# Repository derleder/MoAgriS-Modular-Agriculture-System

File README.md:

# MoAgriS - Modular Agriculture System

## Introduction
MoAgriS is a System to automate plant care with the help of modules for light, water and wind. The modules are plugged onto 3 rods providing power and communication. This way they can be placed individually to fit the plants needs. The project has been developed under Windows but the use of Linux is possible and encouraged.

## Quickstart
There is none. You need to get the PCBs and the components of the [BOM](#bom) first and combine them yourself or let your provider populate everything. [LCSC](https://lcsc.com/) has been quite usefull since they offer a [PCB service](https://jlcpcb.com/) besides the components and the shipment can be combined. A possible PCB configuration can be seen in [PCB/notes/pcb-spec.PNG](./PCB/notes/pcb-spec.PNG). The default values such as PCB thickness or copper weight of 1 oz are fine, too. Unfortunately not all parts can be found there at the time of writing such as the SAMD11 or the PT4115 current regulator.

Once a PCB is ready the SAMD11 needs a [bootloader](https://github.com/mattairtech/ArduinoCore-samd/blob/master/bootloaders/zero/binaries/sam_ba_Generic_D11C14A_SAMD11C14A.bin) by [Mattairtech](https://github.com/mattairtech) to be transmitted via the SWD interface. This is a one-time procedure since the bootloader handles all the firmware updates via USB afterwards. The [Segger J-Link](https://www.segger.com/products/debug-probes/j-link/models/j-link-edu-mini/) comes in handy for that if the licensing is not a problem to you. Other solutions are possible as long as the SAMD11 is supported. Currently I use [Atmel Studio](https://www.microchip.com/mplab/avr-support/atmel-studio-7) for this step (Tools->Device Programming) though the Studio is quite an overkill.

Right now there is no Firmware binary (see [Future](#Future)) so you need to go through the [Development](#Development) section to set up the [Arduino IDE](https://www.arduino.cc/en/main/software). After that you can compile and upload the firmwares found in [Firmware](/Firmware). You need one master on the SDI bus and you can use pretty much as many slaves as you want - tell me if there's a limit. The master can be any PCB that has a SAMD11 if you wish to wish keep your order small. The dedicated master PCB only has power and BUS connectors.

Now that the PCBs are fully working it's time to clamp them on the rods. Plug the master via USB into your PC/Raspberry and open a serial console such as Realterm (Windows) or minicom (Linux). Find out the masters COM-Port (Windows: Device Manager -> COM & LPT ports -> the one thats containing Mattairtech in the description), set the Baud rate to 115200 and connect to it. You should receive a welcoming "Opening SDI-12 bus master..." the first time you connect to the master. It's best to tell your terminal to add a line feed (\n) to a command. This way the master knows to send it over the SDI bus - it's not neccessary since a command is sent anyway after a timeout of 1s.

That's it pretty much. You should be able to send commands to the individual modules now. There's a node-red solution in development to automate it further.

## Alternative Uploading
Since the USB ports are no real benefit they can be left out except for the master board which uses it for serial communication. To achieve that choose [NO_BOOTLOADER in the Arduino Tools Bootloader size menu](https://github.com/mattairtech/ArduinoCore-samd#bootloader-size-menu). After you created/exported the binaries you can use another programmer like Atmel Studio to program directly via the Segger J-Link to the very start of the flash (no address needs to be specified).

The binaries can also be found directly in the corresponding folders under Firmware.

## Development
Thanks to [Mattairtechs ArduinoCore-samd](https://github.com/mattairtech/ArduinoCore-samd) firmware development is quite easy. The setup is described [here](https://github.com/mattairtech/ArduinoCore-samd#installation) (two parts!). The flash size of the SAMD11 is quite small to fit in all the firmware but it is possible if you turn off as many functions as possible in the config.h (Windows: C:\Users\User\AppData\Local\Arduino15\packages\MattairTech_Arduino\hardware\samd\1.6.18-beta-b1\config.h). My config can be found in [Firmware/config.h](./Firmware/config.h). You will save additional flash space by setting serial config under tools to "no_uart_one_wire_one_spi".

You also need to install [Arduino-SDI-12](https://github.com/EnviroDIY/Arduino-SDI-12/releases/tag/v1.1.0) and add it to the Arduino IDE for the <SDI12.h> include. Please use v1.1.0 since newer ones do not seem to work with the SAMD11.

Additionally you should avoid costful code such as the String datatype. Right now the complete firmware for the slave takes up 10232 Bytes.

## SDI Commands
The SDI protocol consists of commands from the master and answers from the sensors in printable 7bit ACII characters. A command starts with an [address](#Addressing) followed by an instruction and an optional parameter. It is finished with an '!' and sent to the module(s). If the command is a heartbeat or a group instruction the module doesn't answer. If a certain module is addressed the answer will be given via the SDI bus starting with its address and an answer. That string is also printed to the serial if you connected the module via USB for debugging purposes.

### Addressing
The modules are addressed by a 4 character lower case hex string which represents two bytes of an SDI address. It is created during bootup in the module by xoring the 3 serial number registers of the SAMD11. Since there is no EEPROM on the controller this seems to be the best solution for getting almost unique addresses. When you install the firmware you should set up a one master one slave system to get the modules address by '?I!' and write it somewhere like the left out rectangle on the module.

Besides addressing a single module you can address multiple ones with a single command. That way you won't receive any answers from the modules though - the master will always send "ACK". The wildcard character '?' will address all modules. If an single upper case letter is used you can address groups. The default group is 'N' as in None. You can set the group of a module by sending 'abcdGL!' ('abcd' = address, 'G' = set group, 'L' = Group L). Remember there is no EEPROM so the group will be lost once the module reboots. Either write a setup routine or set SDIGROUPDEFAULT in the firmware code to keep the group after booting.

### Instructions
Commands should be finished with \n and responses are finished by \r\n by the module itself.

| Instruction | Description | Answer | Example (Command!Response) |
| ----------- | ----------- | ------ | -------------------------- |
| I | Identification | abcd | ?I!abcd |
|||(Address)||
| V | Version | 00.00.02 | abcdV!abcd00.00.02 |
|||(Version)||
| Ccccc | Change address | [new Address] | abcdC1234!1234 |
|| cccc: Address |||
| H | Send Heartbeat to avoid module returning to a save state| - | ?H! |
| Jiiii | Set heartbeat interval | ACK | abcdJ0060!abcdACK |
|| iiii .. Interval in seconds (trailing 0s)
| Gc | Set SDI group | ACK | abcdGL!abcdACK
|| c: Group
| K | Get SDI group | [Group] | abcdK!abcdL
| Si | Set status LED | ACK | abcdS0!abcdACK
|| i: 0 (on), 1 (off) 
| Liii | Set power LED | ACK | abcdL100!abcdACK
|| iii: 000..255 (trailing 0s) || LL255!
| Pi | Set pump | ACK | abcdP1
|| i: 1(on), 0(off)
| Fiii | Set fan | ACK | abcdF100!abcdACK
|| iii: 000..255 (trailing 0s)

## BOM
The [BOM /PCB/notes/BOM.ods](./PCB/notes/BOM.ods) is divided into the BaseBoard which contains the components all modules share except for the Angle. Since some more parts of the BaseBoard are required for certain modules the column "See also" tells you where to look. 
There is also a [Accessories /PCB/notes/Accessories.ods](./PCB/notes/Accessories.ods) list to find some ideas about the other utensils.

## Modules
All modules are created in [Eagle](https://www.autodesk.com/products/eagle/overview) and are within the 10cm*10cm limit to use the free version.

### LED-Module 
Provides light by 3 full spectrum LEDs which intensity can be controlled via SDI. The long version has a better light and heat distribution.

### Pump-Module 
Provides water by a pump by switching it on/off via SDI. 

### Fan-Module_40mm
Provides wind by a 40mm fan that can be controlled via PWM over SDI.

### Fan-Module_80mm
Provides wind by a 80mm fan that can be controlled via PWM over SDI. This is it. That's the limit of the free Eagle version. The fuseholders sit so tightly to the fan that you might need to chop off their legs.

### SDI-Master
Optional board to be used as a SDI master. You can use any other module as a master but this one is optimized for the job. It is as slim as the LED PCB and has two possible power connectors - only use one. The screw connector also has a third terminal to also chain the BUS signal.

### Angle
Provides an ~90° angle for the rods. 

## Node-RED
You need the following plugins to make the [flow configuration in flow.json](./Node-RED/flow.json) working:

- [node-red-node-serialport](https://flows.nodered.org/node/node-red-node-serialport)
- [node-red-contrib-simple-message-queue](https://flows.nodered.org/node/node-red-contrib-simple-message-queue)

The subflow handles incoming commands or arrays of commands by means of putting them into a queue, calculating the expected response and retrying the command 3 times on false responses. It also adds "!\n" to each input so you only have to enter the pure command. The flow itself demonstrates the use of a heartbeat that beats every 10s and a setup routine that sets the heartbeat interval and the sensors' group. Additionally there is a timed injection which starts the leds at 8am and shuts them down at 5pm. After the demo setup routine you may address all the leds at once by their group address but it is not advised since you won't get an answer and so the subflow can not check if the communication worked. If there's an error you may send an email.

After importing the flow you need to configure the serial port by configuring the MoAgriS-Subflow (double click on the MoAgriS node -> Edit subflow template -> double click on the serial request node - it's the one after the queue).

If you wish to have a dashboard like the one below the plugin [node-red-dashboard](https://flows.nodered.org/node/node-red-dashboard) helps you.

## Future
More things could be added such as
- Sensors: Currently all SDI slave boards are technically capable of driving sensors since all pins are routed outside:
	- Watering could depend on the wetness of the soil
	- Measure the water level of the pump tank to send an alert to refill
- Find an alternative to Atmel Studio for installing the bootloader
- Provide firmware binaries to avoid setting up Arduino IDE

## Bugs
- Modules don't answer after hours of no use
- Sometimes there's a voltage on the BUS of 0.1-2.5V
- Sometimes the BUS only works when a logic analyzer is attached to GND/BUS
- Sometimes it helps to connect the programmers reset pin when you need to reprogramm the bootloader

## More
<br />This work is licensed under a <a rel="license" href="http://creativecommons.org/licenses/by-sa/4.0/">Creative Commons Attribution-ShareAlike 4.0 International License</a>.

For more details see https://hackaday.io/project/91757-moagris-modular-agriculture-system

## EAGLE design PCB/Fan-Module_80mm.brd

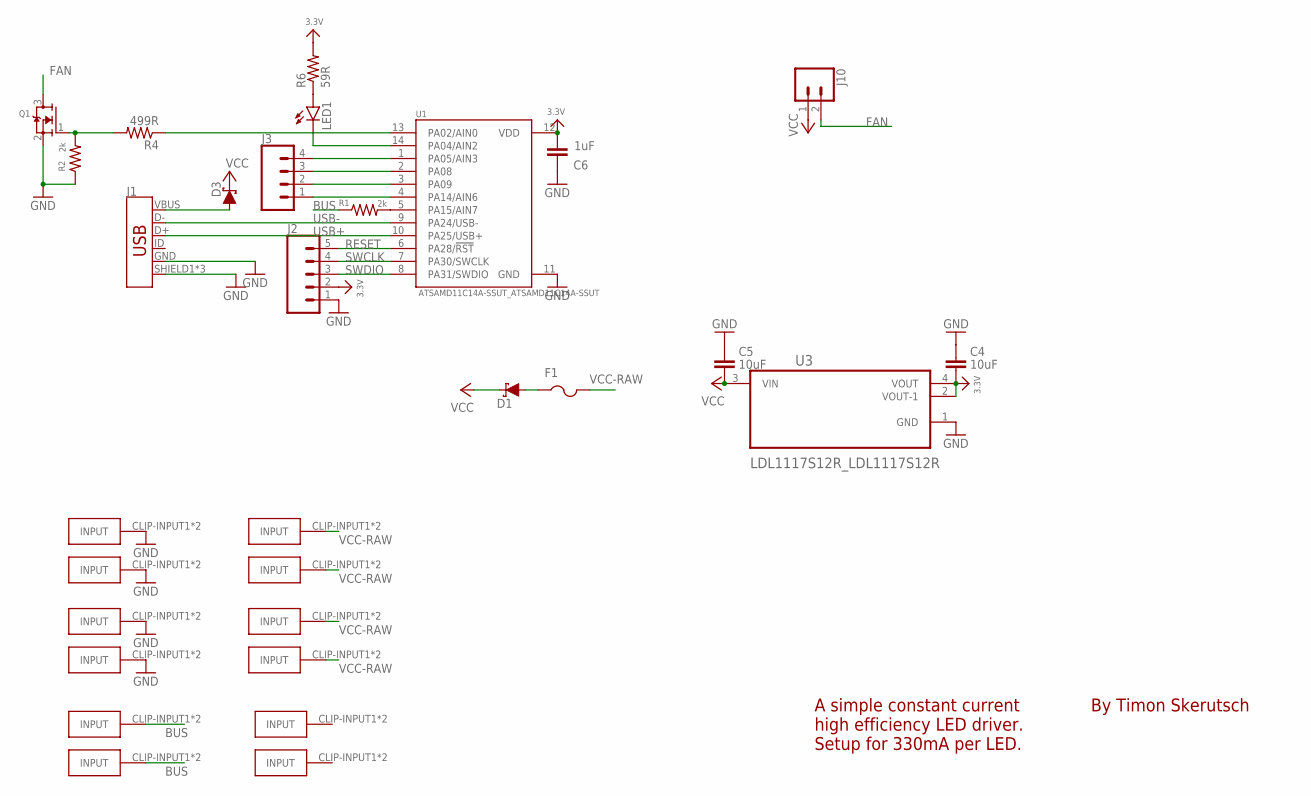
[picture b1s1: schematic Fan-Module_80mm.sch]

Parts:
C4, C5: 10uF; C0603
C6: 1uF; C0603
D1, D3: 3A/40V/500mV; SMA-DIODE
F1: PTCFUSE-1812; 1812
GND-CLIP, GND-CLIP1, GND-CLIP2, GND-CLIP3: FUSE-HOLDER-5X20MM
J1: USB_MICRO-B_FEMALE-SMT; USB-B-MICRO-SMD
J2: CONN_05; 1X05
J3: CONN_04PTH; 1X04
J10: CONN_02PTH3; 1X02_LONGPADS
LED1: LEDCHIPLED_0805; CHIPLED_0805
PWM-CLIP, PWM-CLIP1, PWM-CLIP2, PWM-CLIP3: FUSE-HOLDER-5X20MM
Q1: MOSFET-NWIDE; SOT23-WIDE
R1, R2: 2k; R1206
R4: 499R; R0805
R6: 59R; R0805
U1: ATSAMD11C14A-SSUT_ATSAMD11C14A-SSUT; ATSAMD11C14A-SSUT_SOIC127P600X160-14N
U3: LDL1117S12R_LDL1117S12R; LDL1117S12R_SOT230P700X180-4N
VCC-CLIP, VCC-CLIP1, VCC-CLIP2, VCC-CLIP3: FUSE-HOLDER-5X20MM

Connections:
3.3V: C4.2, C6.2, J2.2, R6.2, U1.12 (VDD), U3.2 (VOUT-1), U3.4 (VOUT)
BUS: PWM-CLIP.CLIP-INPUT1, PWM-CLIP.CLIP-INPUT2, PWM-CLIP1.CLIP-INPUT1, PWM-CLIP1.CLIP-INPUT2, R1.1
FAN: J10.2, Q1.3 (D)
GND: C4.1, C5.1, C6.1, GND-CLIP.CLIP-INPUT1, GND-CLIP.CLIP-INPUT2, GND-CLIP1.CLIP-INPUT1, GND-CLIP1.CLIP-INPUT2, GND-CLIP2.CLIP-INPUT1, GND-CLIP2.CLIP-INPUT2, GND-CLIP3.CLIP-INPUT1, GND-CLIP3.CLIP-INPUT2, J1.GND, J1.SHIELD1 (SHIELD), J1.SHIELD2 (SHIELD), J1.SHIELD3 (SHIELD), J2.1, Q1.2 (S), R2.1, U1.11 (GND), U3.1 (GND)
unnamed: LED1.C, U1.14 (PA04/AIN2)
unnamed: LED1.A, R6.1
unnamed: R1.2, U1.5 (PA15/AIN7)
unnamed: D3.A, J1.VBUS
unnamed: R4.1, U1.13 (PA02/AIN0)
unnamed: D1.A, F1.1
unnamed: J3.4, U1.1 (PA05/AIN3)
unnamed: Q1.1 (G), R2.2, R4.2
unnamed: J3.3, U1.2 (PA08)
unnamed: J3.2, U1.3 (PA09)
unnamed: J3.1, U1.4 (PA14/AIN6)
RESET: J2.5, U1.6 (PA28/!RST)
SWCLK: J2.4, U1.7 (PA30/SWCLK)
SWDIO: J2.3, U1.8 (PA31/SWDIO)
USB+: J1.D+, U1.10 (PA25/USB+)
USB-: J1.D-, U1.9 (PA24/USB-)
VCC: C5.2, D1.C, D3.C, J10.1, U3.3 (VIN)
VCC-RAW: F1.2, VCC-CLIP.CLIP-INPUT1, VCC-CLIP.CLIP-INPUT2, VCC-CLIP1.CLIP-INPUT1, VCC-CLIP1.CLIP-INPUT2, VCC-CLIP2.CLIP-INPUT1, VCC-CLIP2.CLIP-INPUT2, VCC-CLIP3.CLIP-INPUT1, VCC-CLIP3.CLIP-INPUT2

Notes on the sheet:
By Timon Skerutsch
A simple constant current high efficiency LED driver. Setup for 330mA per LED.

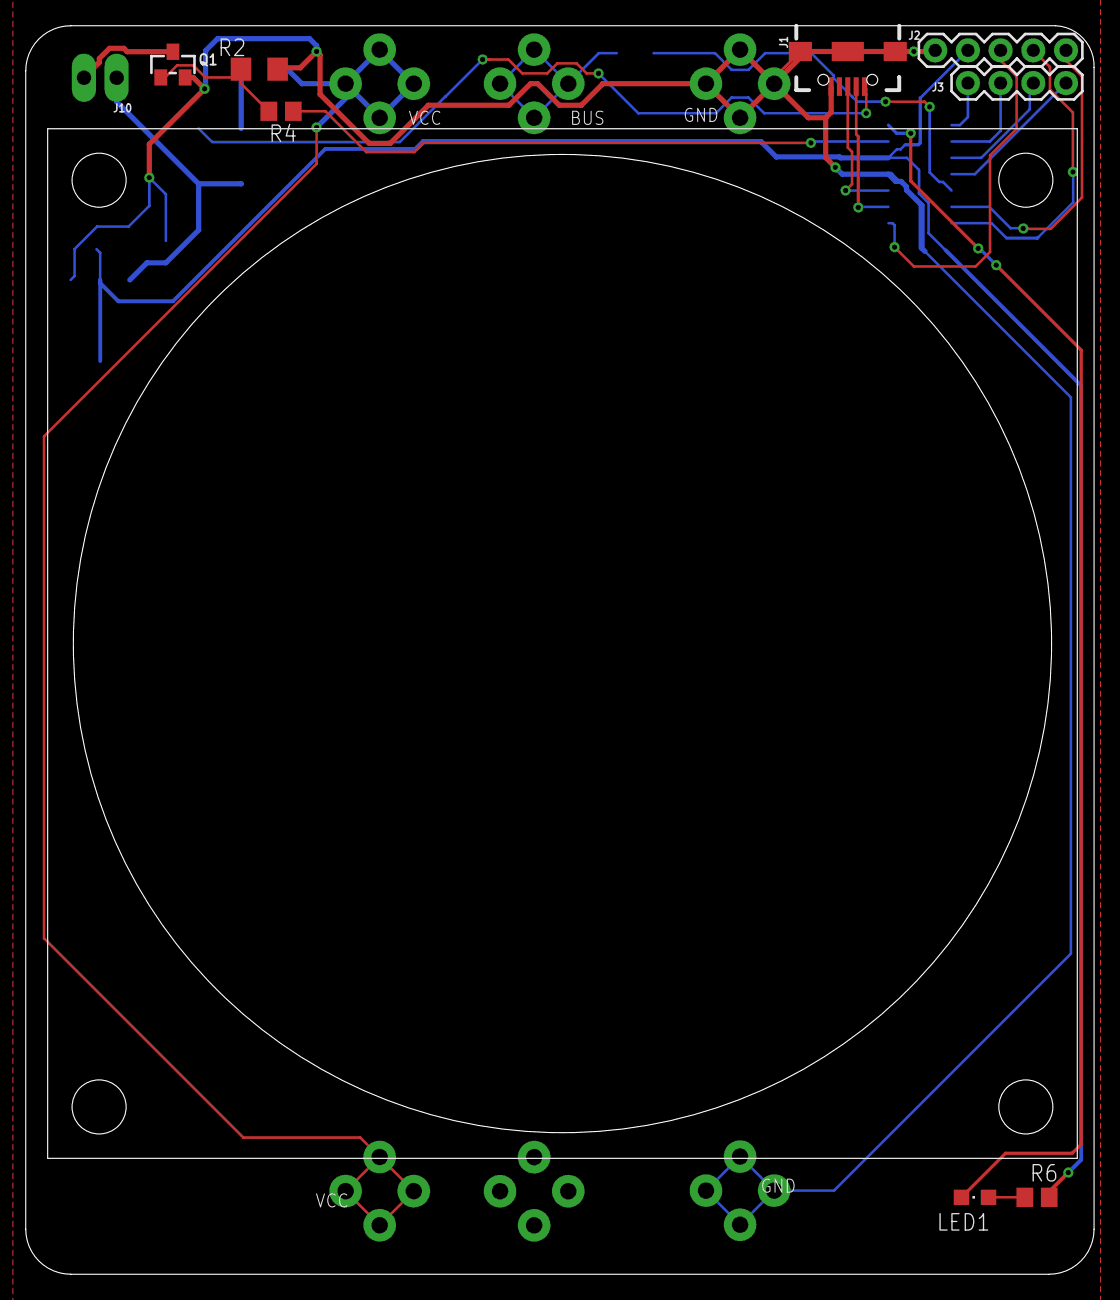
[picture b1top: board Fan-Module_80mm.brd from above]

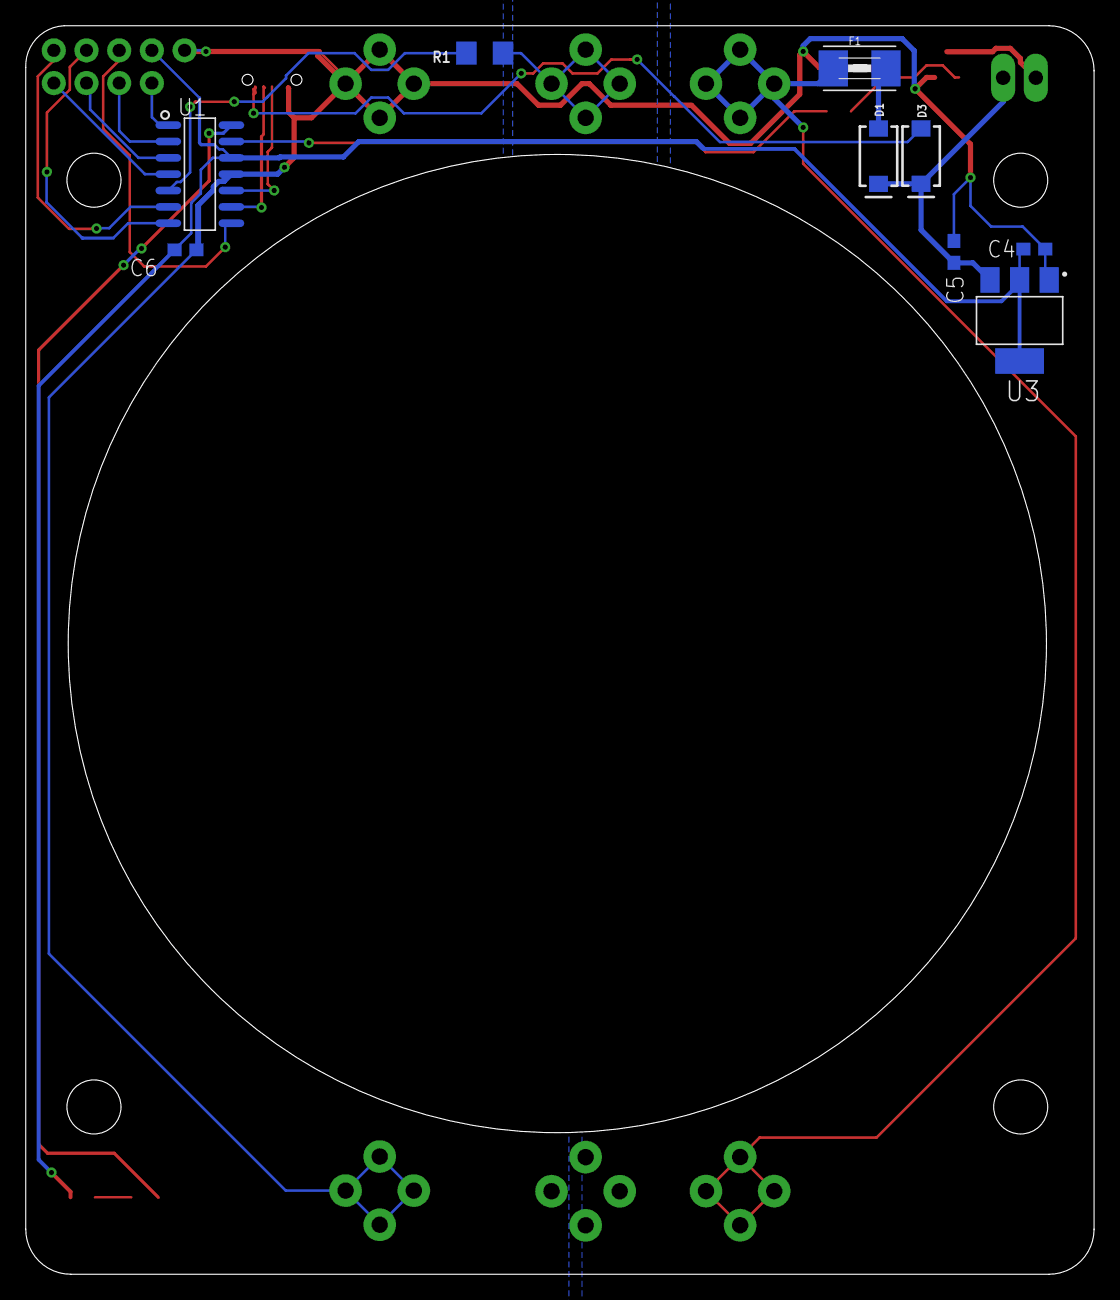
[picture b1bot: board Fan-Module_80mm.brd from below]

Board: 2 copper layers, 83.0 x 97.0 mm, 31 parts (10 on the bottom side), 22 nets.

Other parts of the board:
U10: 80MM-FAN

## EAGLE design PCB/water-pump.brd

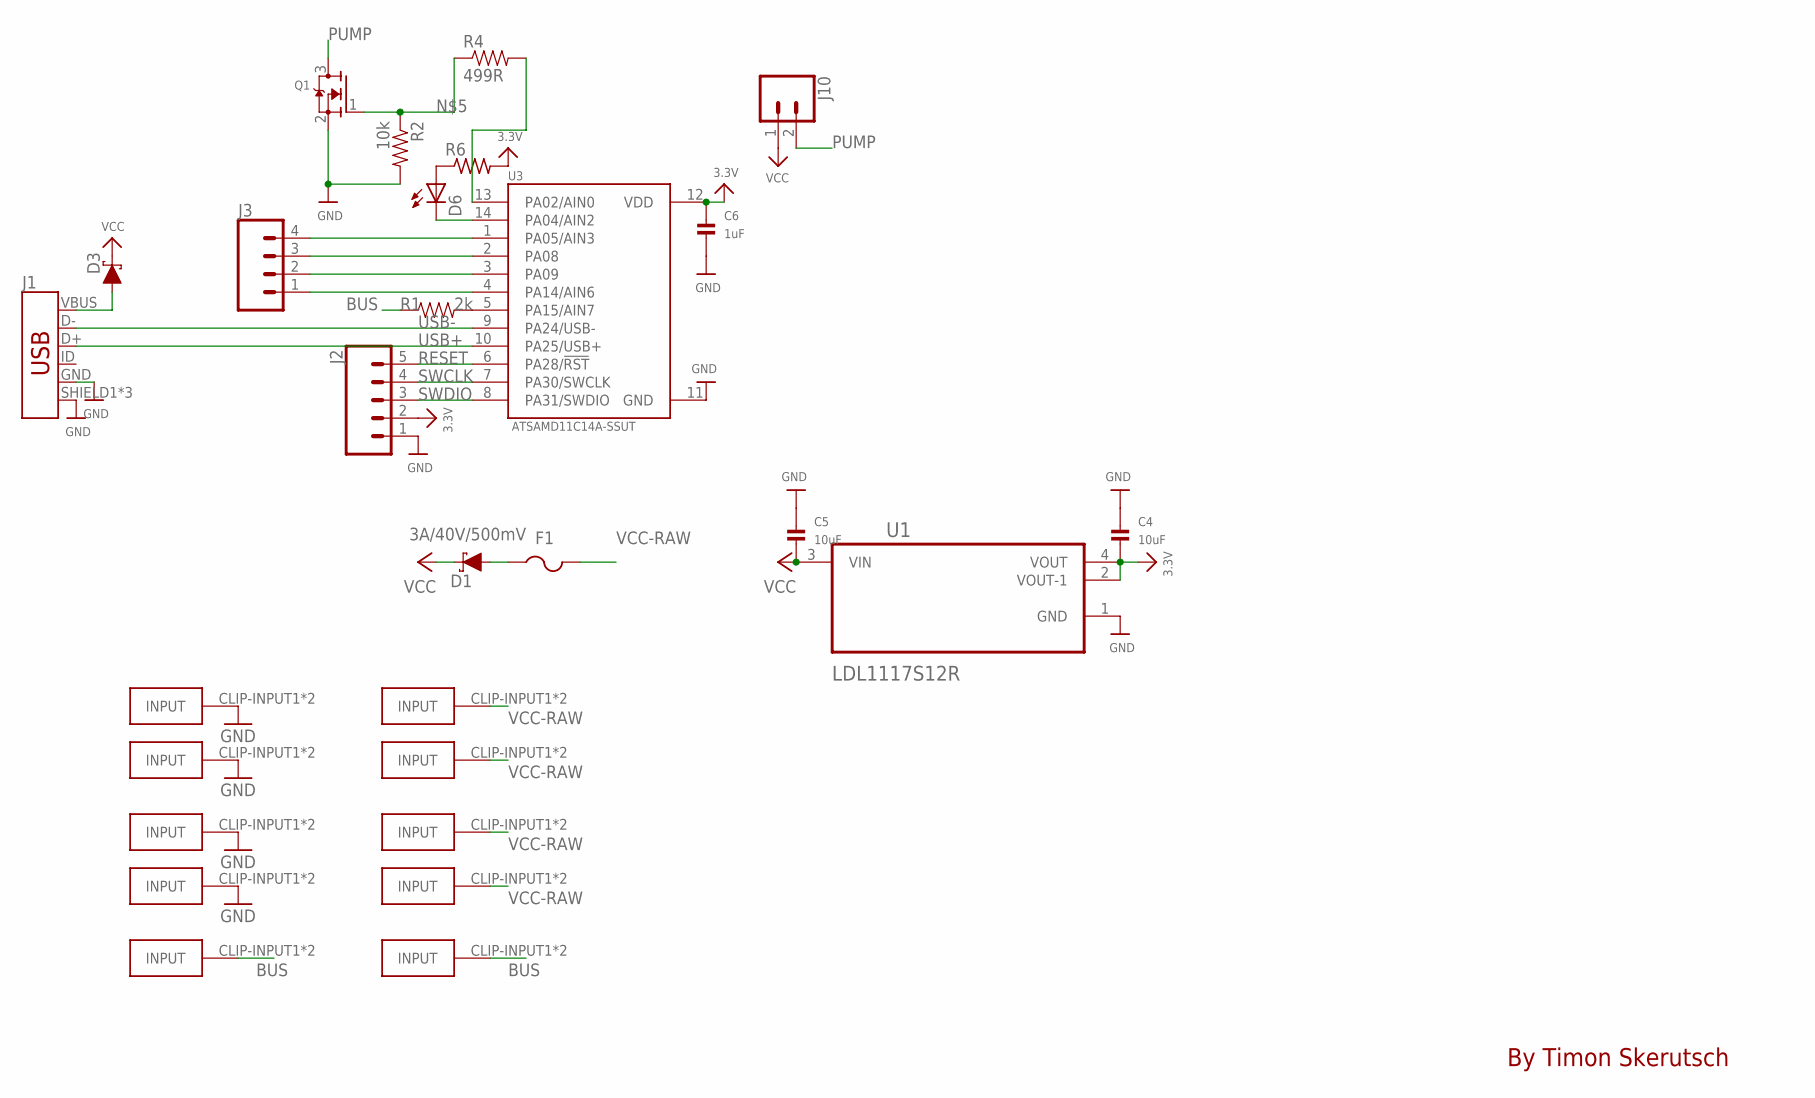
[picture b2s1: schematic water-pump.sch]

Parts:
C4, C5: 10uF; 0805
C6: 1uF; 0603
D1, D3: 3A/40V/500mV; SMA-DIODE
D6: LEDCHIPLED_0805; CHIPLED_0805
F1: PTCFUSE-1812; 1812
GND-CLIP, GND-CLIP1, GND-CLIP2, GND-CLIP3: FUSE-HOLDER-5X20MM
J1: USB_MICRO-B_FEMALE-SMT; USB-B-MICRO-SMD
J2: CONN_05; 1X05
J3: CONN_04PTH; 1X04
J10: CONN_02PTH3; 1X02_LONGPADS
PWM-CLIP, PWM-CLIP1: FUSE-HOLDER-5X20MM
Q1: MOSFET-NWIDE; SOT23-WIDE
R1: 2k; 1206
R2: 10k; 1206
R4: 499R; 1206
R6: R-US_R0805; R0805
U1: LDL1117S12R; SOT230P700X180-4N
U3: ATSAMD11C14A-SSUT; SOIC127P600X160-14N
VCC-CLIP, VCC-CLIP1, VCC-CLIP2, VCC-CLIP3: FUSE-HOLDER-5X20MM

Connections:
3.3V: C4.2, C6.1, J2.2, R6.2, U1.2 (VOUT-1), U1.4 (VOUT), U3.12 (VDD)
BUS: PWM-CLIP.CLIP-INPUT1, PWM-CLIP.CLIP-INPUT2, PWM-CLIP1.CLIP-INPUT1, PWM-CLIP1.CLIP-INPUT2, R1.1
GND: C4.1, C5.1, C6.2, GND-CLIP.CLIP-INPUT1, GND-CLIP.CLIP-INPUT2, GND-CLIP1.CLIP-INPUT1, GND-CLIP1.CLIP-INPUT2, GND-CLIP2.CLIP-INPUT1, GND-CLIP2.CLIP-INPUT2, GND-CLIP3.CLIP-INPUT1, GND-CLIP3.CLIP-INPUT2, J1.GND, J1.SHIELD1 (SHIELD), J1.SHIELD2 (SHIELD), J1.SHIELD3 (SHIELD), J2.1, Q1.2 (S), R2.2, U1.1 (GND), U3.11 (GND)
unnamed: D3.A, J1.VBUS
unnamed: R1.2, U3.5 (PA15/AIN7)
unnamed: J3.4, U3.1 (PA05/AIN3)
unnamed: Q1.1 (G), R2.1, R4.1
unnamed: D1.A, F1.1
unnamed: D6.A, R6.1
unnamed: D6.C, U3.14 (PA04/AIN2)
unnamed: J3.3, U3.2 (PA08)
unnamed: J3.2, U3.3 (PA09)
unnamed: J3.1, U3.4 (PA14/AIN6)
PUMP: J10.2, Q1.3 (D)
PUMP_CTRL: R4.2, U3.13 (PA02/AIN0)
RESET: J2.5, U3.6 (PA28/!RST)
SWCLK: J2.4, U3.7 (PA30/SWCLK)
SWDIO: J2.3, U3.8 (PA31/SWDIO)
USB+: J1.D+, U3.10 (PA25/USB+)
USB-: J1.D-, U3.9 (PA24/USB-)
VCC: C5.2, D1.C, D3.C, J10.1, U1.3 (VIN)
VCC-RAW: F1.2, VCC-CLIP.CLIP-INPUT1, VCC-CLIP.CLIP-INPUT2, VCC-CLIP1.CLIP-INPUT1, VCC-CLIP1.CLIP-INPUT2, VCC-CLIP2.CLIP-INPUT1, VCC-CLIP2.CLIP-INPUT2, VCC-CLIP3.CLIP-INPUT1, VCC-CLIP3.CLIP-INPUT2

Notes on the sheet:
By Timon Skerutsch

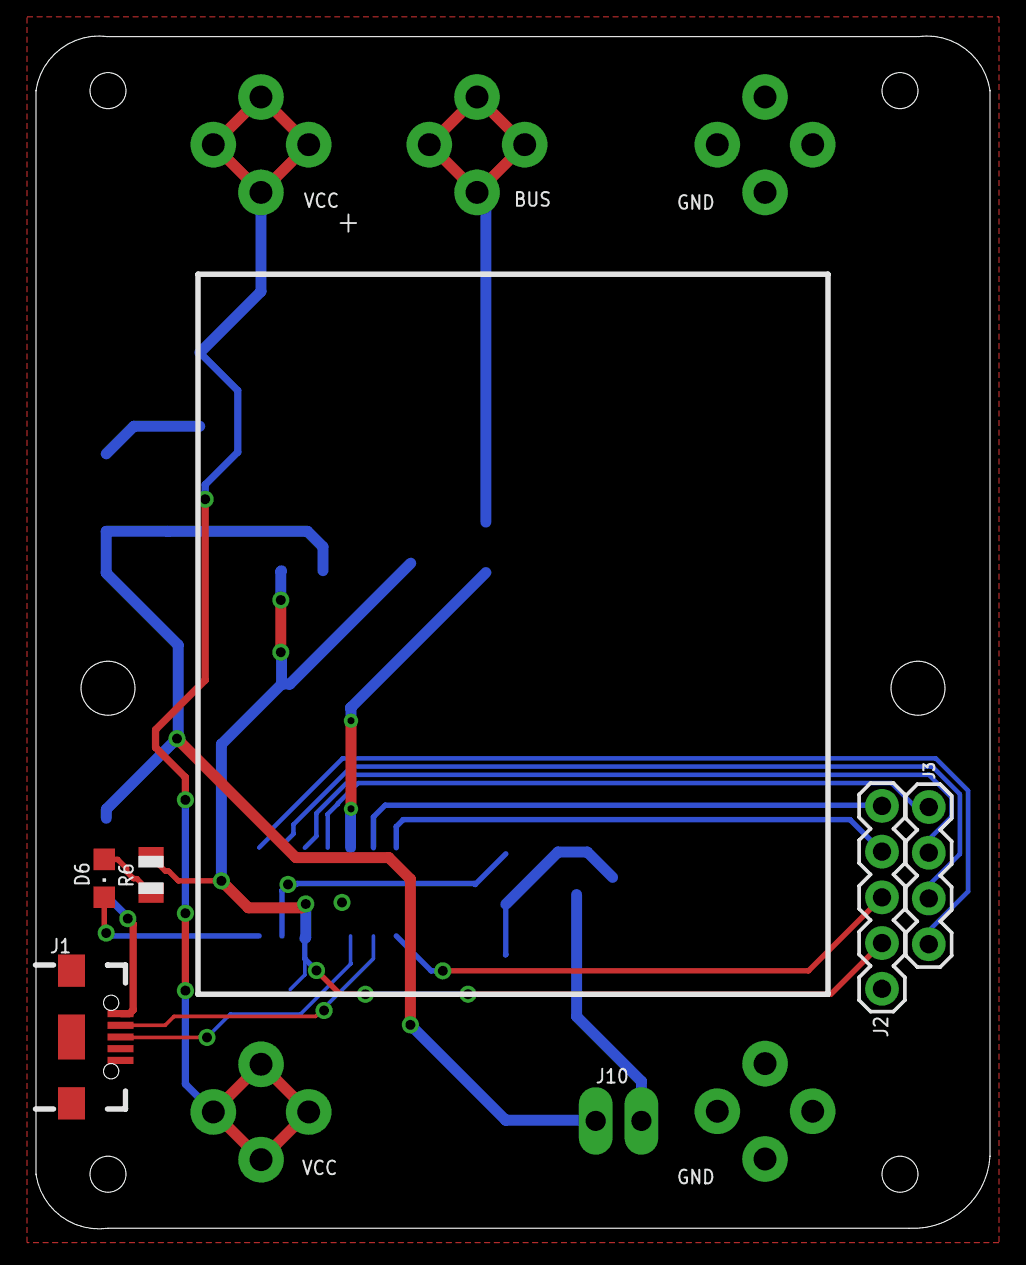
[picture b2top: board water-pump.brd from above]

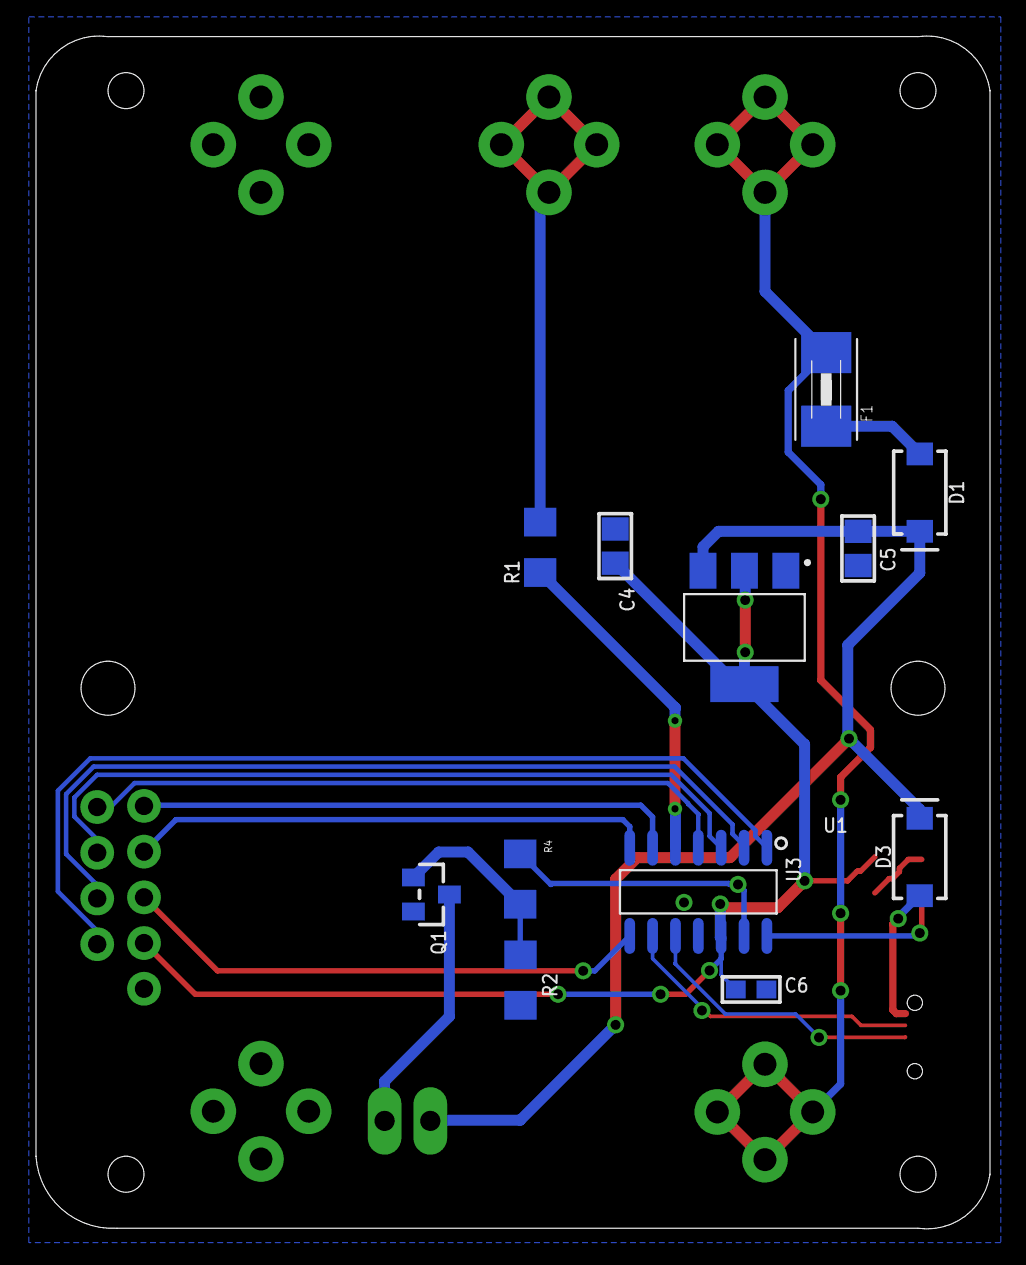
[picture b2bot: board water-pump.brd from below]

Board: 2 copper layers, 53.0 x 66.3 mm, 28 parts (22 on the bottom side), 22 nets.

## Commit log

2019-04-08 removed thermals from canvas to improve heat transportation to the rods
2019-04-11 tried to debug sdi communication by adding a cmd timeout
2019-04-11 removed master printing incomming cmd to serial for node-red
2019-04-13 added node red configuration and doc
2019-04-13 forgot to save...
2019-04-13 added heatsinks to bom for testing
2019-04-26 added 4pin connector for remaining pins on all boards
2019-04-26 forgot to send slave address on ?I!
2019-04-30 added 80mm fan and renamed small 40mm fan
2019-04-30 modified sdi master to suit sdi application node
2019-04-30 updated BOM
2019-09-22 unknown changes, break has been too long
2020-06-06 added save pump command
2020-06-07 added bug workaround to readme
2020-06-07 slave prints address on serial start
2020-06-07 workaround for using action pin in analog and digital mode
2020-12-12 fixed master bug receiving address from unknown board, updated readme to program without usb port

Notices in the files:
parts and their libraries:
SparkFun-DiscreteSemi: Licensing: Creative Commons ShareAlike 4.0 International - https://creativecommons.org/licenses/by-sa/4.0
microbuilder: This work is placed in the public domain, and may be freely used for commercial and non-commercial work with the following conditions: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
